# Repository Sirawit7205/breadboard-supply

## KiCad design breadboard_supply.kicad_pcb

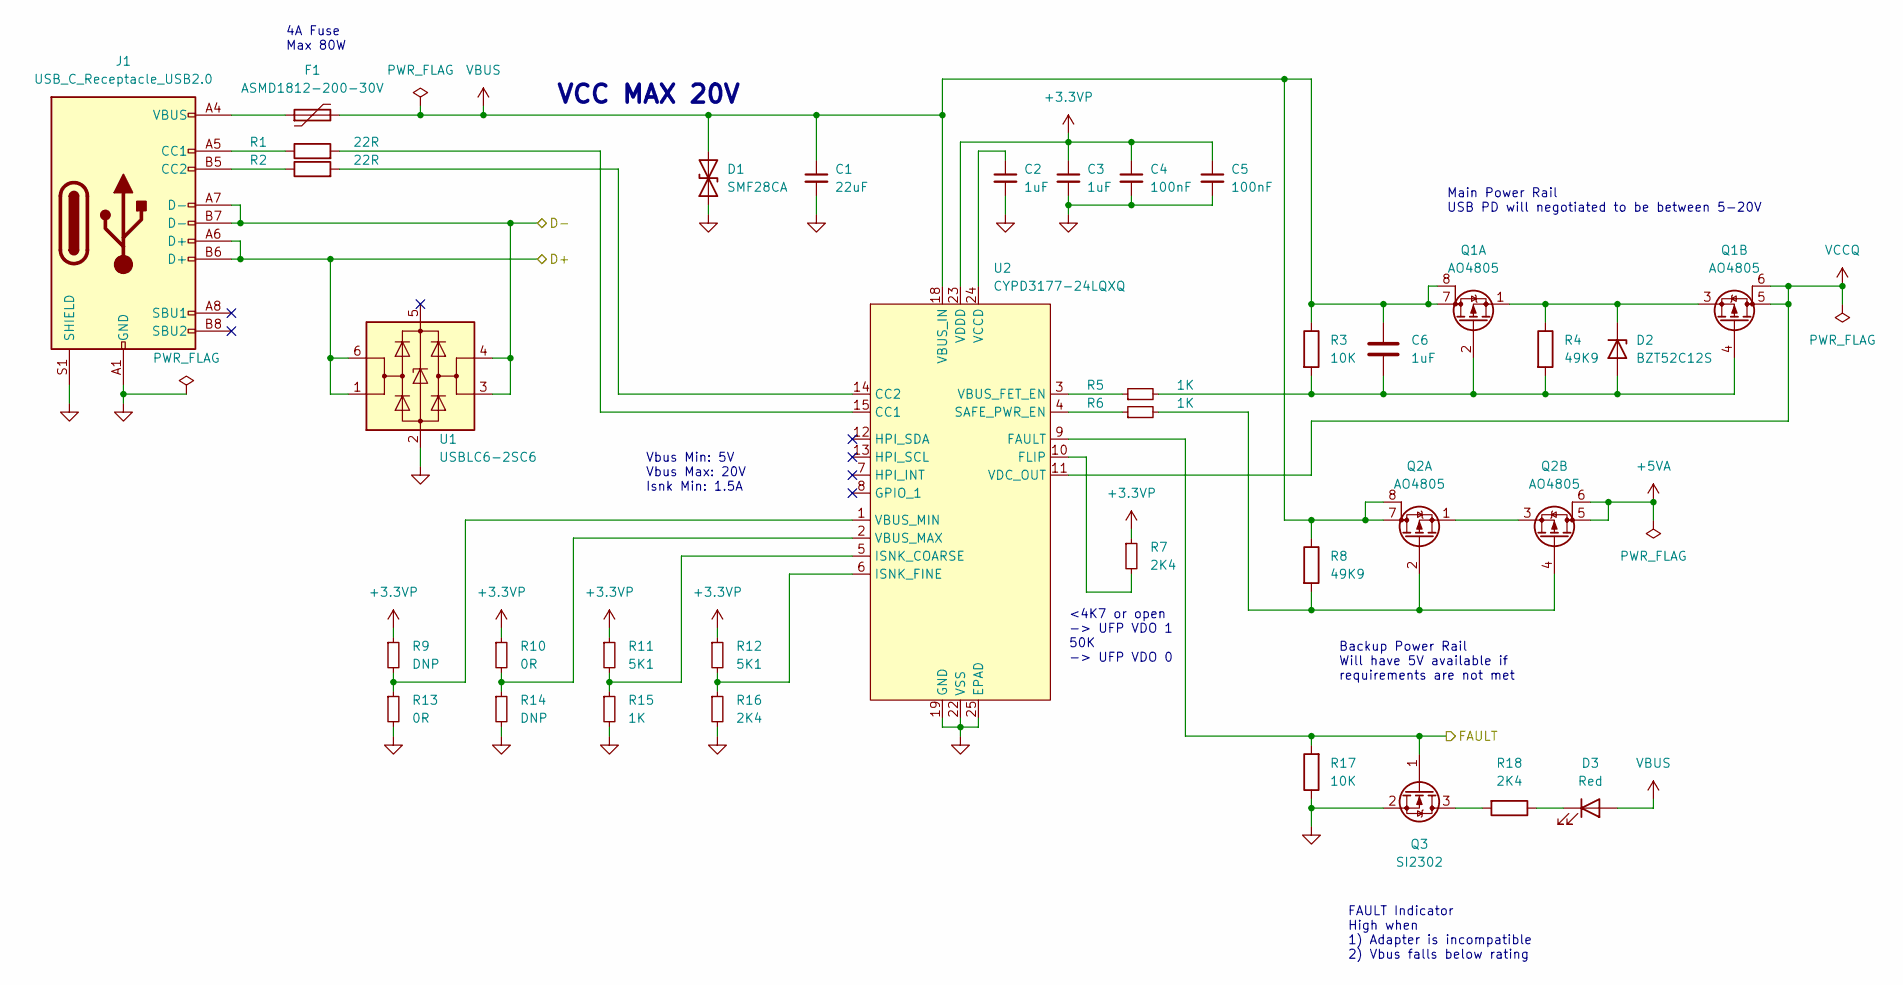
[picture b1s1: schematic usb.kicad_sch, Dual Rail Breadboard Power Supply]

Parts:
C1: 22uF; C_1210_3225Metric; MPN 22uF 25V X7R
C2, C3, C6: 1uF; C_0603_1608Metric; MPN 1uF 50V X7R
C4, C5: 100nF; C_0603_1608Metric; MPN 100nF 50V X7R
D1: SMF28CA; D_SOD-123; MPN SMF28CA
D2: BZT52C12S; D_SOD-323; MPN BZT52C12S
D3: Red; LED_0603_1608Metric; MPN KT-0603R
F1: ASMD1812-200-30V; Fuse_1812_4532Metric; MPN ASMD1812-200-30V
J1: USB_C_Receptacle_USB2.0; USB_C_Receptacle_HRO_TYPE-C-31-M-12_NO_SBU_CircularHoles; MPN HC-TYPE-C-16P-01A
Q1, Q2: AO4805; SOIC-8_3.9x4.9mm_P1.27mm; MPN AO4805
Q3: SI2302; SOT-23
R1, R2: 22R; R_0603_1608Metric; MPN 22R 1%
R3, R17: 10K; R_0603_1608Metric; MPN 10K 1%
R4, R8: 49K9; R_0603_1608Metric; MPN 49K9 1%
R5, R6, R15: 1K; R_0603_1608Metric; MPN 1K 1%
R7: 2K4; R_0603_1608Metric; MPN 3K3 1%
R9, R14: DNP; R_0603_1608Metric
R10, R13: 0R; R_0603_1608Metric; MPN 0R 1%
R11, R12: 5K1; R_0603_1608Metric; MPN 5K1 1%
R16, R18: 2K4; R_0603_1608Metric; MPN 2K4 1%
U1: USBLC6-2SC6; SOT-23-6; MPN USBLC6-2SC6
U2: CYPD3177-24LQXQ; QFN-24-1EP_4x4mm_P0.5mm_EP2.7x2.7mm; MPN CYPD3177-24LQXQ

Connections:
+3.3VP: C3.1, C4.1, C5.1, R7.1, R9.1, R10.1, R11.1, R12.1, U2.23 (VDDD)
+5VA: Q2.5 (D), Q2.6 (G); also elsewhere on the board
/Microcontroller/D+: J1.A6 (D+), J1.B6 (D+), U1.1 (I/O1), U1.6 (I/O1); also elsewhere on the board
/Microcontroller/D-: J1.A7 (D-), J1.B7 (D-), U1.3 (I/O2), U1.4 (I/O2); also elsewhere on the board
/Microcontroller/PD_FAULT: Q3.1 (G), R17.2, U2.9 (FAULT); also elsewhere on the board
GND: C1.2, C2.2, C3.2, C4.2, C5.2, D1.1 (A1), J1.A1 (GND), J1.A12 (GND), J1.B1 (GND), J1.B12 (GND), J1.S1 (SHIELD), Q3.2 (S), R13.2, R14.2, R15.2, R16.2, R17.1, U1.2 (GND), U2.19 (GND), U2.22 (VSS), U2.25 (EPAD); also elsewhere on the board
unnamed: C2.1, U2.24 (VCCD)
unnamed: C6.2, D2.2 (A), Q1.2 (G), Q1.4 (G), R3.2, R4.2, R5.2
unnamed: D2.1 (K), Q1.1 (S), Q1.3 (S), R4.1
unnamed: D3.1 (K), R18.1
unnamed: F1.1, J1.A4 (VBUS), J1.A9 (VBUS), J1.B4 (VBUS), J1.B9 (VBUS)
unnamed: J1.A5 (CC1), R1.1
unnamed: J1.B5 (CC2), R2.1
unnamed: Q2.1 (S), Q2.3 (S)
unnamed: Q2.2 (G), Q2.4 (G), R6.2, R8.2
unnamed: Q3.3 (D), R18.2
unnamed: R1.2, U2.15 (CC1)
unnamed: R2.2, U2.14 (CC2)
unnamed: R5.1, U2.3 (VBUS_FET_EN)
unnamed: R6.1, U2.4 (SAFE_PWR_EN)
unnamed: R7.2, U2.10 (FLIP)
unnamed: R10.2, R14.1, U2.2 (VBUS_MAX)
unnamed: R11.2, R15.1, U2.5 (ISNK_COARSE)
unnamed: R12.2, R16.1, U2.6 (ISNK_FINE)
unnamed: R9.2, R13.1, U2.1 (VBUS_MIN)
VBUS: C1.1, C6.1, D1.2 (A2), D3.2 (A), F1.2, Q1.7 (D), Q1.8 (G), Q2.7 (D), Q2.8 (G), R3.1, R8.1, U2.18 (VBUS_IN)
VCCQ: Q1.5 (D), Q1.6 (G), U2.11 (VDC_OUT); also elsewhere on the board

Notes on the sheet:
Vbus Min: 5V Vbus Max: 20V Isnk Min: 1.5A
4A Fuse Max 80W
Main Power Rail USB PD will negotiated to be between 5-20V
VCC MAX 20V
<4K7 or open -> UFP VDO 1 50K -> UFP VDO 0
FAULT Indicator High when 1) Adapter is incompatible 2) Vbus falls below rating
Backup Power Rail Will have 5V available if requirements are not met

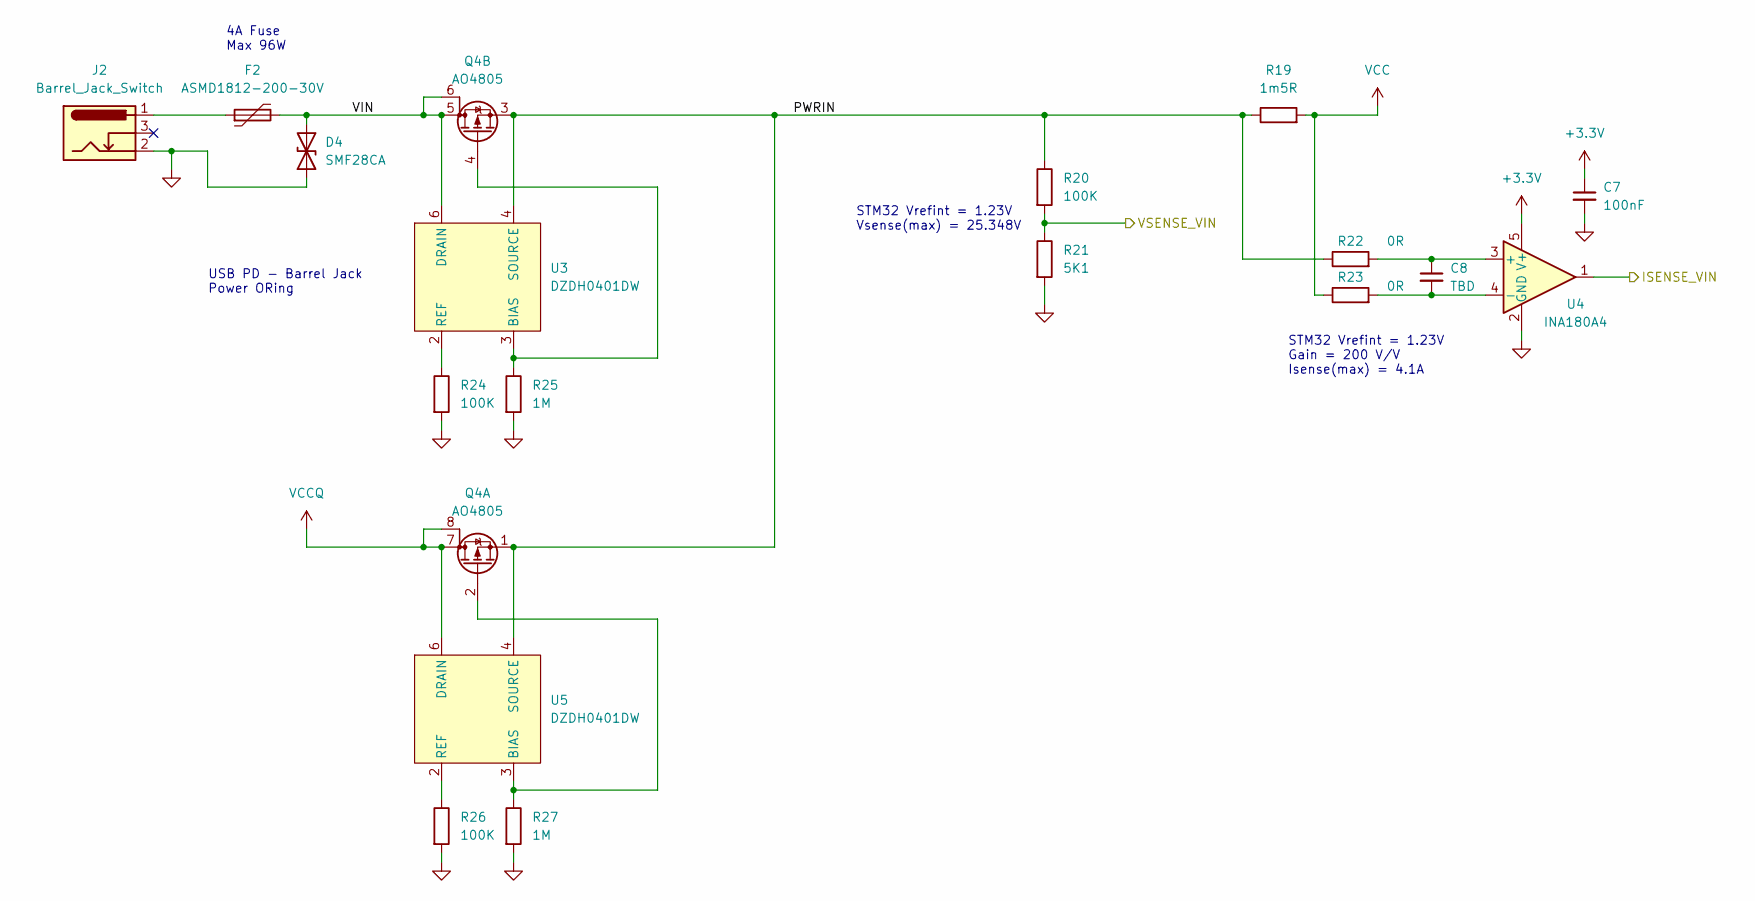
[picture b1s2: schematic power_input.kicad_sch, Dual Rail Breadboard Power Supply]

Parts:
C7: 100nF; C_0603_1608Metric; MPN 100nF 50V X7R
C8: TBD; C_0603_1608Metric
D4: SMF28CA; D_SOD-123; MPN SMF28CA
F2: ASMD1812-200-30V; Fuse_1812_4532Metric; MPN ASMD1812-200-30V
J2: Barrel_Jack_Switch; BarrelJack_Horizontal; MPN DC-005-5A-2.0
Q4: AO4805; SOIC-8_3.9x4.9mm_P1.27mm; MPN AO4805
R19: 1m5R; R_2512_6332Metric; MPN 1m5R 1%
R20, R24, R26: 100K; R_0603_1608Metric; MPN 100K 1%
R21: 5K1; R_0603_1608Metric; MPN 5K1 1%
R22, R23: 0R; R_0603_1608Metric; MPN 0R 1%
R25, R27: 1M; R_0603_1608Metric; MPN 1M 1%
U3, U5: DZDH0401DW; SOT-363_SC-70-6; MPN DZDH0401DW-7
U4: INA180A4; SOT-23-5; MPN INA180A4IDBVR

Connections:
+3.3V: C7.1, U4.5 (V+); also elsewhere on the board
/Microcontroller/ISENSE_VIN: U4.1; also elsewhere on the board
/Microcontroller/VSENSE_VIN: R20.2, R21.1; also elsewhere on the board
/Power Input/PWRIN: Q4.1 (S), Q4.3 (S), R19.1, R20.1, R22.1, U3.4 (SOURCE), U5.4 (SOURCE)
/Power Input/VIN: D4.2 (A2), F2.2, Q4.5 (D), Q4.6 (G), U3.6 (DRAIN)
GND: C7.2, D4.1 (A1), J2.2, R21.2, R24.2, R25.2, R26.2, R27.2, U4.2 (GND); also elsewhere on the board
unnamed: C8.1, R22.2, U4.3 (+)
unnamed: C8.2, R23.2, U4.4 (-)
unnamed: F2.1, J2.1
unnamed: Q4.2 (G), R27.1, U5.3 (BIAS)
unnamed: Q4.4 (G), R25.1, U3.3 (BIAS)
unnamed: R24.1, U3.2 (REF)
unnamed: R26.1, U5.2 (REF)
VCC: R19.2, R23.1; also elsewhere on the board
VCCQ: Q4.7 (D), Q4.8 (G), U5.6 (DRAIN); also elsewhere on the board

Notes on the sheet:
4A Fuse Max 96W
STM32 Vrefint = 1.23V Vsense(max) = 25.348V
STM32 Vrefint = 1.23V Gain = 200 V/V Isense(max) = 4.1A
USB PD - Barrel Jack Power ORing

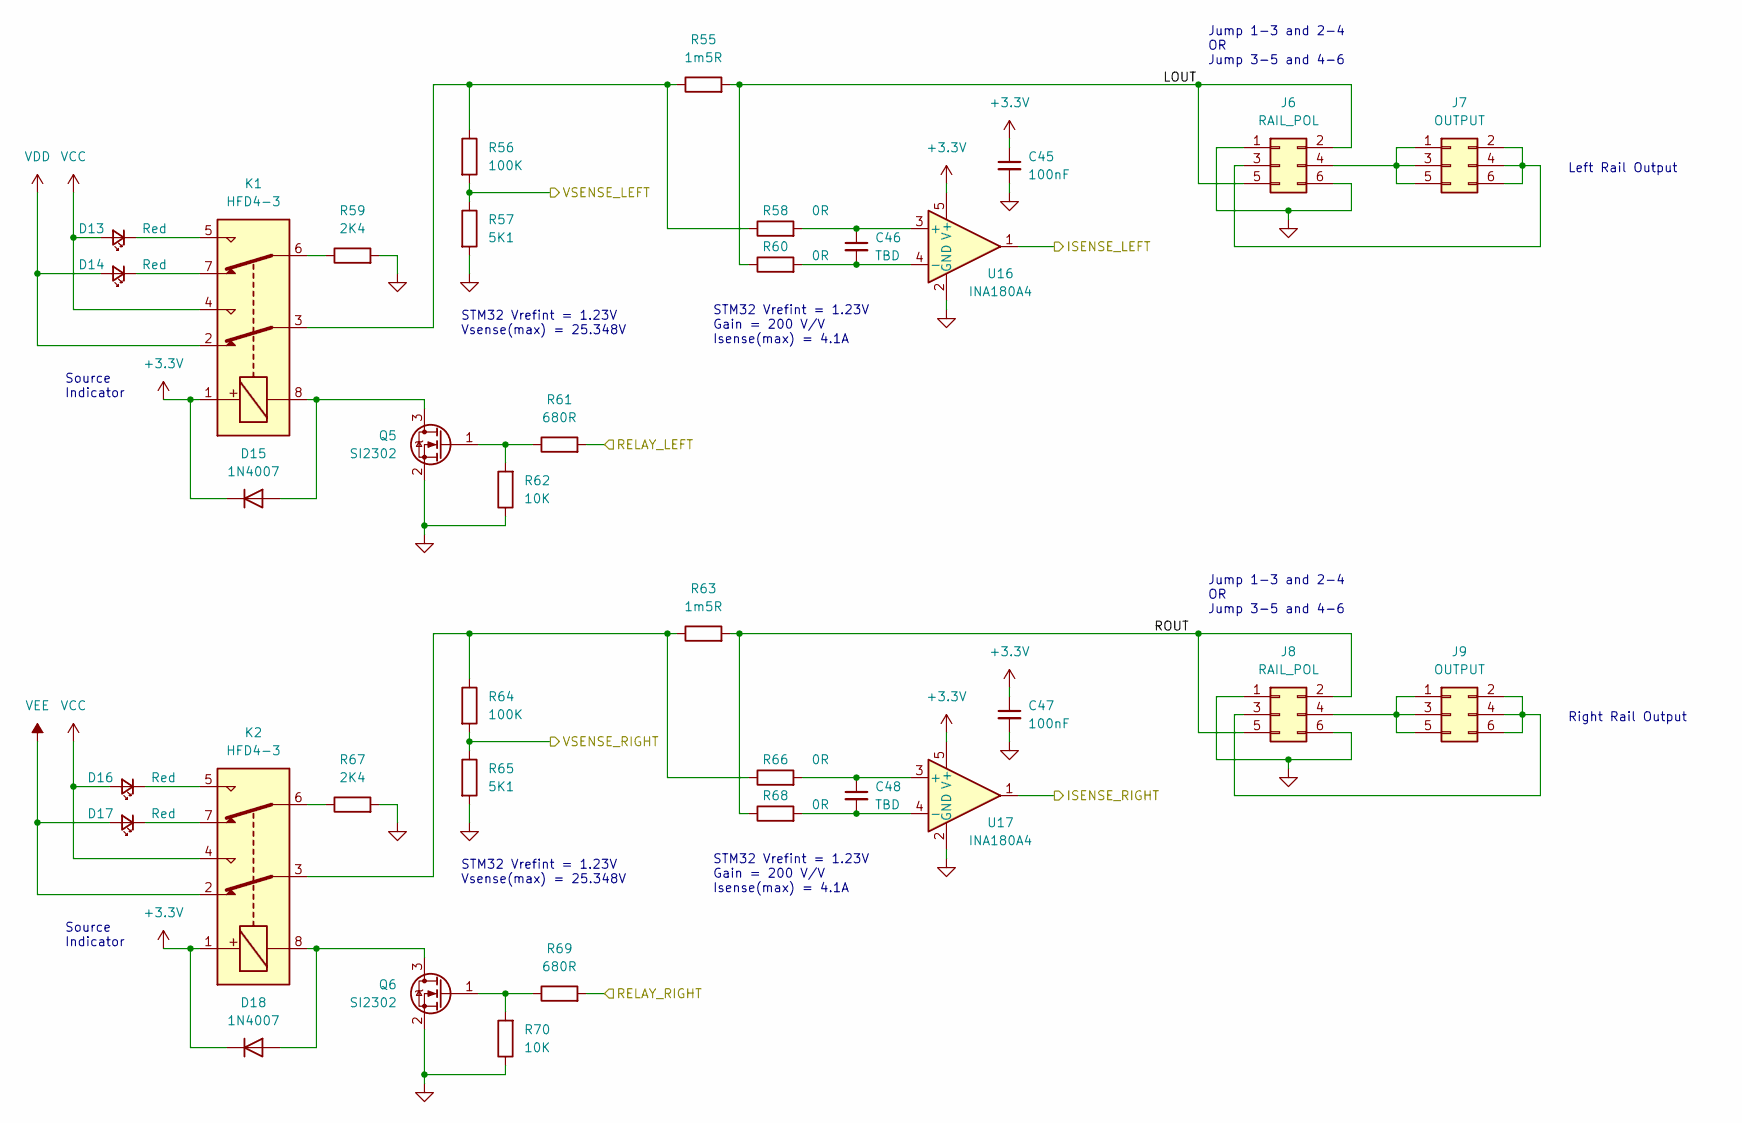
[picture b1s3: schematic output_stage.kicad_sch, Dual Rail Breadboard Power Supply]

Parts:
C45, C47: 100nF; C_0603_1608Metric; MPN 100nF 50V X7R
C46, C48: TBD; C_0603_1608Metric
D13, D14, D16, D17: Red; LED_0603_1608Metric; MPN KT-0603R
D15, D18: 1N4007; D_SOD-123; MPN A7
J6, J8: RAIL_POL; PinHeader_2x03_P2.54mm_Vertical
J7, J9: OUTPUT; PinHeader_2x03_P2.54mm_Vertical
K1, K2: HFD4-3; HFD4; MPN HFD4/3-SR
Q5, Q6: SI2302; SOT-23; MPN SI2302
R55, R63: 1m5R; R_2512_6332Metric; MPN 1m5R 1%
R56, R64: 100K; R_0603_1608Metric; MPN 100K 1%
R57, R65: 5K1; R_0603_1608Metric; MPN 5K1 1%
R58, R60, R66, R68: 0R; R_0603_1608Metric; MPN 0R 1%
R59, R67: 2K4; R_0603_1608Metric; MPN 2K4 1%
R61, R69: 680R; R_0603_1608Metric; MPN 680R 1%
R62, R70: 10K; R_0603_1608Metric; MPN 10K 1%
U16, U17: INA180A4; SOT-23-5; MPN INA180A4IDBVR

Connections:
+3.3V: C45.1, C47.1, D15.1 (K), D18.1 (K), K1.1, K2.1, U16.5 (V+), U17.5 (V+); also elsewhere on the board
/Microcontroller/ISENSE_LEFT: U16.1; also elsewhere on the board
/Microcontroller/ISENSE_RIGHT: U17.1; also elsewhere on the board
/Microcontroller/RELAY_LEFT: R61.2; also elsewhere on the board
/Microcontroller/RELAY_RIGHT: R69.2; also elsewhere on the board
/Microcontroller/VSENSE_LEFT: R56.2, R57.1; also elsewhere on the board
/Microcontroller/VSENSE_RIGHT: R64.2, R65.1; also elsewhere on the board
/Output Stage/LOUT: J6.2, J6.5, R55.2, R60.1
/Output Stage/ROUT: J8.2, J8.5, R63.2, R68.1
GND: C45.2, C47.2, J6.1, J6.6, J8.1, J8.6, Q5.2 (S), Q6.2 (S), R57.2, R59.2, R62.1, R65.2, R67.2, R70.1, U16.2 (GND), U17.2 (GND); also elsewhere on the board
unnamed: C46.1, R58.2, U16.3 (+)
unnamed: C46.2, R60.2, U16.4 (-)
unnamed: C48.1, R66.2, U17.3 (+)
unnamed: C48.2, R68.2, U17.4 (-)
unnamed: D13.1 (K), K1.5
unnamed: D14.1 (K), K1.7
unnamed: D15.2 (A), K1.8, Q5.3 (D)
unnamed: D16.1 (K), K2.5
unnamed: D17.1 (K), K2.7
unnamed: D18.2 (A), K2.8, Q6.3 (D)
unnamed: J6.3, J7.2, J7.4, J7.6
unnamed: J6.4, J7.1, J7.3, J7.5
unnamed: J8.3, J9.2, J9.4, J9.6
unnamed: J8.4, J9.1, J9.3, J9.5
unnamed: K1.3, R55.1, R56.1, R58.1
unnamed: K1.6, R59.1
unnamed: K2.3, R63.1, R64.1, R66.1
unnamed: K2.6, R67.1
unnamed: Q5.1 (G), R61.1, R62.2
unnamed: Q6.1 (G), R69.1, R70.2
VCC: D13.2 (A), D16.2 (A), K1.4, K2.4; also elsewhere on the board
VDD: D14.2 (A), K1.2; also elsewhere on the board
VEE: D17.2 (A), K2.2; also elsewhere on the board

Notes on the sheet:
STM32 Vrefint = 1.23V Vsense(max) = 25.348V
Left Rail Output
Source Indicator
Right Rail Output
Jump 1-3 and 2-4 OR Jump 3-5 and 4-6
STM32 Vrefint = 1.23V Gain = 200 V/V Isense(max) = 4.1A

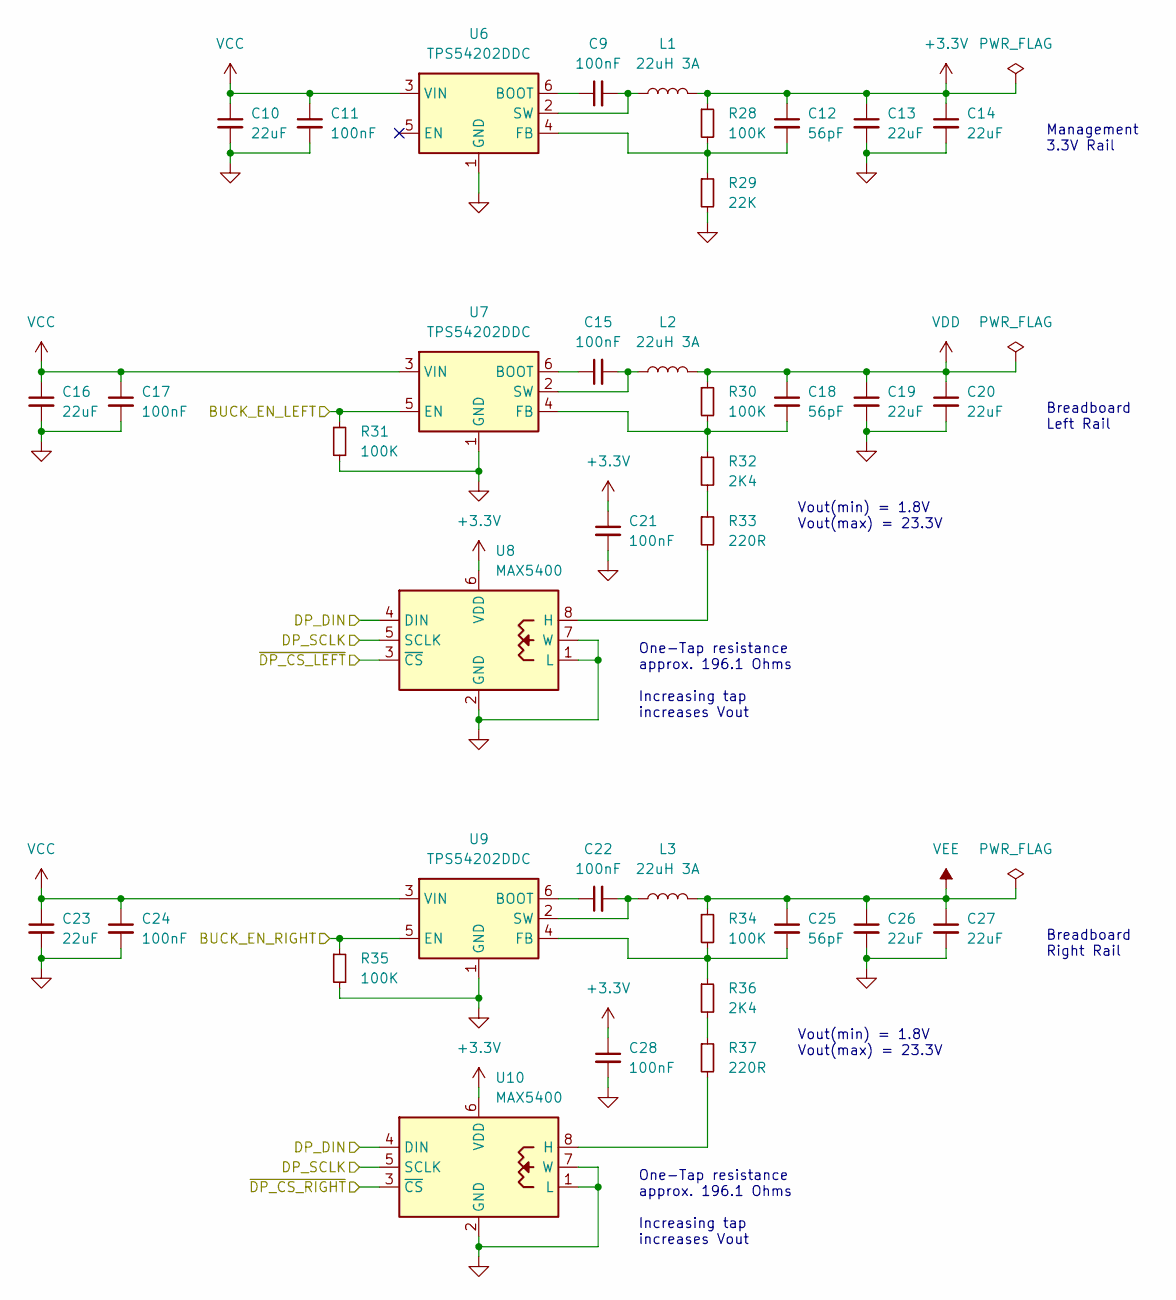
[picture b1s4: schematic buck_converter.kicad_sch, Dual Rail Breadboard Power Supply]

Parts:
C9, C11, C15, C17, C21, C22, C24, C28: 100nF; C_0603_1608Metric; MPN 100nF 50V X7R
C10, C13, C14, C16, C19, C20, C23, C26, C27: 22uF; C_1210_3225Metric; MPN 22uF 25V X7R
C12, C18, C25: 56pF; C_0603_1608Metric; MPN 56pF 50V C0G
L1, L2, L3: 22uH 3A; L_Bourns_SRN6045TA; MPN SRN6045TA-220M
R28, R30, R31, R34, R35: 100K; R_0603_1608Metric; MPN 100K 1%
R29: 22K; R_0603_1608Metric; MPN 22K 1%
R32, R36: 2K4; R_0603_1608Metric; MPN 2K4 1%
R33, R37: 220R; R_0603_1608Metric; MPN 220R 1%
U6, U7, U9: TPS54202DDC; SOT-23-6; MPN TPS54202DDCR
U8, U10: MAX5400; SOT-23-8; MPN MAX5400EKA+T

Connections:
+3.3V: C12.1, C13.1, C14.1, C21.1, C28.1, L1.2, R28.1, U8.6 (VDD), U10.6 (VDD); also elsewhere on the board
/Buck Converter/BUCK_EN_LEFT: R31.1, U7.5 (EN); also elsewhere on the board
/Buck Converter/BUCK_EN_RIGHT: R35.1, U9.5 (EN); also elsewhere on the board
/Buck Converter/DP_DIN: U8.4 (DIN), U10.4 (DIN); also elsewhere on the board
/Buck Converter/DP_SCLK: U8.5 (SCLK), U10.5 (SCLK); also elsewhere on the board
/Buck Converter/~DP_CS_LEFT: U8.3 (~CS); also elsewhere on the board
/Buck Converter/~DP_CS_RIGHT: U10.3 (~CS); also elsewhere on the board
GND: C10.2, C11.2, C13.2, C14.2, C16.2, C17.2, C19.2, C20.2, C21.2, C23.2, C24.2, C26.2, C27.2, C28.2, R29.2, R31.2, R35.2, U6.1 (GND), U7.1 (GND), U8.1 (L), U8.2 (GND), U8.7 (W), U9.1 (GND), U10.1 (L), U10.2 (GND), U10.7 (W); also elsewhere on the board
unnamed: C9.1, U6.6 (BOOT)
unnamed: C9.2, L1.1, U6.2 (SW)
unnamed: C12.2, R28.2, R29.1, U6.4 (FB)
unnamed: C15.1, U7.6 (BOOT)
unnamed: C15.2, L2.1, U7.2 (SW)
unnamed: C18.2, R30.2, R32.1, U7.4 (FB)
unnamed: C22.1, U9.6 (BOOT)
unnamed: C22.2, L3.1, U9.2 (SW)
unnamed: C25.2, R34.2, R36.1, U9.4 (FB)
unnamed: R32.2, R33.1
unnamed: R33.2, U8.8 (H)
unnamed: R36.2, R37.1
unnamed: R37.2, U10.8 (H)
VCC: C10.1, C11.1, C16.1, C17.1, C23.1, C24.1, U6.3 (VIN), U7.3 (VIN), U9.3 (VIN); also elsewhere on the board
VDD: C18.1, C19.1, C20.1, L2.2, R30.1; also elsewhere on the board
VEE: C25.1, C26.1, C27.1, L3.2, R34.1; also elsewhere on the board

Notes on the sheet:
Vout(min) = 1.8V Vout(max) = 23.3V
Breadboard Right Rail
One-Tap resistance approx. 196.1 Ohms Increasing tap increases Vout
Breadboard Left Rail
Management 3.3V Rail

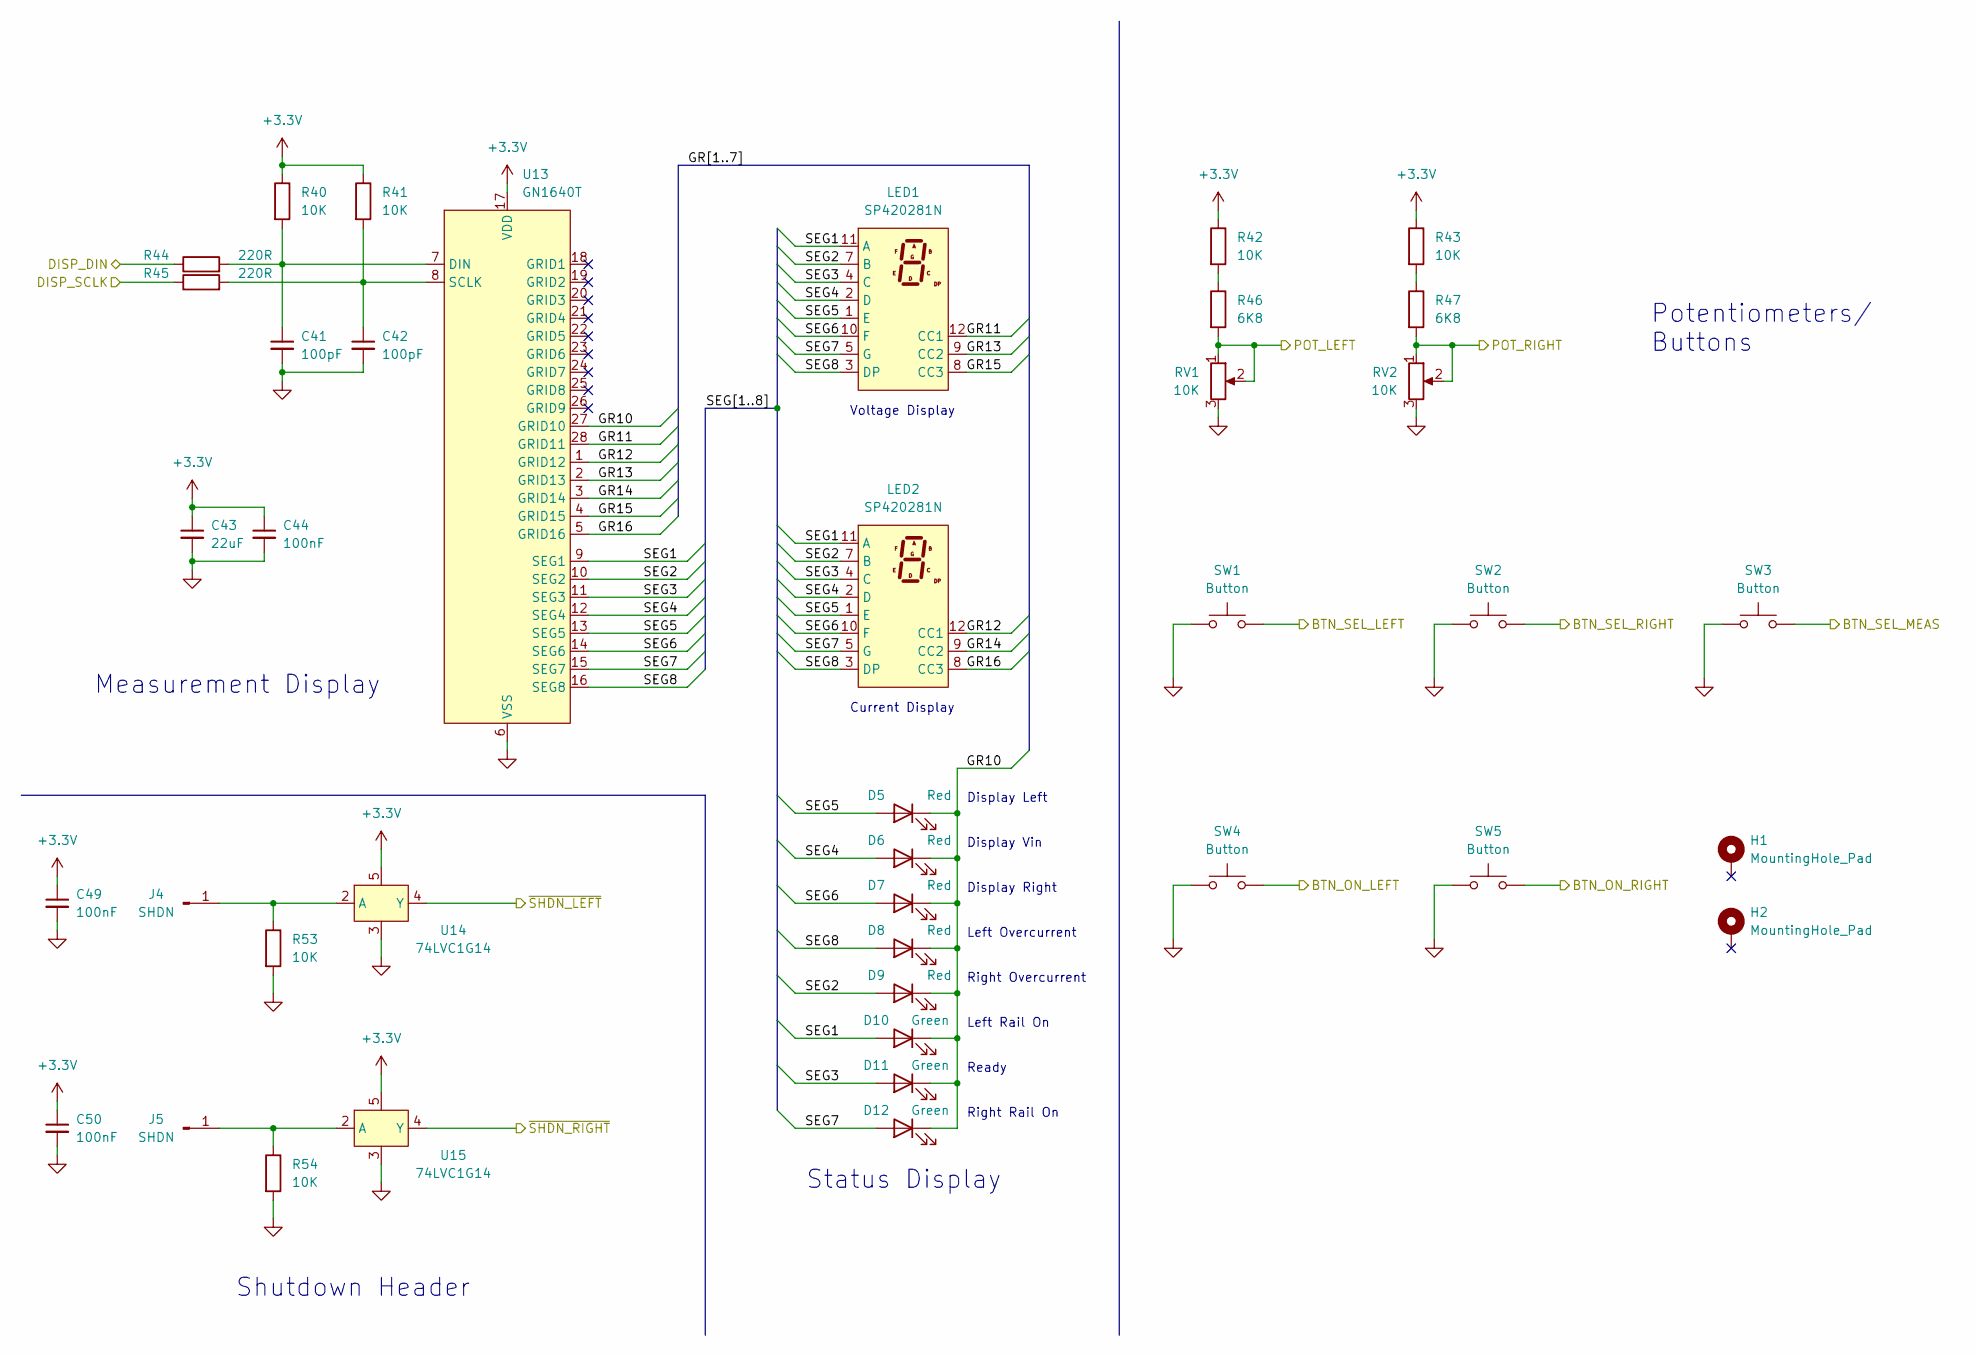
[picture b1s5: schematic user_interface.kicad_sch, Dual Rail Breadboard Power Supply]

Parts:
C41, C42: 100pF; C_0603_1608Metric; MPN 100pF 50V C0G
C43: 22uF; C_1210_3225Metric; MPN 22uF 25V X7R
C44, C49, C50: 100nF; C_0603_1608Metric; MPN 100nF 50V X7R
D5, D6, D7, D8, D9: Red; LED_0603_1608Metric; MPN KT-0603R
D10, D11, D12: Green; LED_0603_1608Metric; MPN 19-217/GHC-YR1S2/3T
H1, H2: MountingHole_Pad; MountingHole_3.2mm_M3_Pad
J4, J5: SHDN; PinHeader_1x01_P2.54mm_Vertical
LED1, LED2: SP420281N; MPN SP420281N
R40, R41, R42, R43, R53, R54: 10K; R_0603_1608Metric; MPN 10K 1%
R44, R45: 220R; R_0603_1608Metric; MPN 220R 1%
R46, R47: 6K8; R_0603_1608Metric; MPN 6K8 1%
RV1, RV2: 10K; Potentiometer_Bourns_3386P_Vertical; MPN 3386P-1-103TLF
SW1, SW2, SW3, SW4, SW5: Button; SW_SPST_CK_RS282G05A3; MPN TS-1101-C-W
U13: GN1640T; SSOP-28_3.9x9.9mm_P0.635mm; MPN GN1640T
U14, U15: 74LVC1G14; SOT-353_SC-70-5; MPN 74LVC1G14GW,125

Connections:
+3.3V: C43.1, C44.1, C49.1, C50.1, R40.1, R41.1, R42.1, R43.1, U13.17 (VDD), U14.5, U15.5; also elsewhere on the board
/Microcontroller/BTN_ON_LEFT: SW4.2; also elsewhere on the board
/Microcontroller/BTN_ON_RIGHT: SW5.2; also elsewhere on the board
/Microcontroller/BTN_SEL_LEFT: SW1.2; also elsewhere on the board
/Microcontroller/BTN_SEL_MEAS: SW3.2; also elsewhere on the board
/Microcontroller/BTN_SEL_RIGHT: SW2.2; also elsewhere on the board
/Microcontroller/POT_LEFT: R46.2, RV1.1, RV1.2; also elsewhere on the board
/Microcontroller/POT_RIGHT: R47.2, RV2.1, RV2.2; also elsewhere on the board
/Microcontroller/SPI2_MOSI: R44.1; also elsewhere on the board
/Microcontroller/SPI2_SCK: R45.1; also elsewhere on the board
/Microcontroller/~SHDN_LEFT: U14.4 (Y); also elsewhere on the board
/Microcontroller/~SHDN_RIGHT: U15.4 (Y); also elsewhere on the board
/User Interface/GR10: D5.1 (K), D6.1 (K), D7.1 (K), D8.1 (K), D9.1 (K), D10.1 (K), D11.1 (K), D12.1 (K), U13.27 (GRID10)
/User Interface/GR11: LED1.12 (CC1), U13.28 (GRID11)
/User Interface/GR12: LED2.12 (CC1), U13.1 (GRID12)
/User Interface/GR13: LED1.9 (CC2), U13.2 (GRID13)
/User Interface/GR14: LED2.9 (CC2), U13.3 (GRID14)
/User Interface/GR15: LED1.8 (CC3), U13.4 (GRID15)
/User Interface/GR16: LED2.8 (CC3), U13.5 (GRID16)
/User Interface/SEG1: D10.2 (A), LED1.11 (A), LED2.11 (A), U13.9 (SEG1)
/User Interface/SEG2: D9.2 (A), LED1.7 (B), LED2.7 (B), U13.10 (SEG2)
/User Interface/SEG3: D11.2 (A), LED1.4 (C), LED2.4 (C), U13.11 (SEG3)
/User Interface/SEG4: D6.2 (A), LED1.2 (D), LED2.2 (D), U13.12 (SEG4)
/User Interface/SEG5: D5.2 (A), LED1.1 (E), LED2.1 (E), U13.13 (SEG5)
/User Interface/SEG6: D7.2 (A), LED1.10 (F), LED2.10 (F), U13.14 (SEG6)
/User Interface/SEG7: D12.2 (A), LED1.5 (G), LED2.5 (G), U13.15 (SEG7)
/User Interface/SEG8: D8.2 (A), LED1.3 (DP), LED2.3 (DP), U13.16 (SEG8)
GND: C41.2, C42.2, C43.2, C44.2, C49.2, C50.2, R53.2, R54.2, RV1.3, RV2.3, SW1.1, SW2.1, SW3.1, SW4.1, SW5.1, U13.6 (VSS), U14.3, U15.3; also elsewhere on the board
unnamed: C41.1, R40.2, R44.2, U13.7 (DIN)
unnamed: C42.1, R41.2, R45.2, U13.8 (SCLK)
unnamed: J4.1, R53.1, U14.2 (A)
unnamed: J5.1, R54.1, U15.2 (A)
unnamed: R42.2, R46.1
unnamed: R43.2, R47.1

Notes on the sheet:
Display Left
Voltage Display
Display Right
Shutdown Header
Left Rail On
Ready
Display Vin
Right Rail On
Right Overcurrent
Current Display
Measurement Display
Potentiometers/ Buttons
Left Overcurrent
Status Display

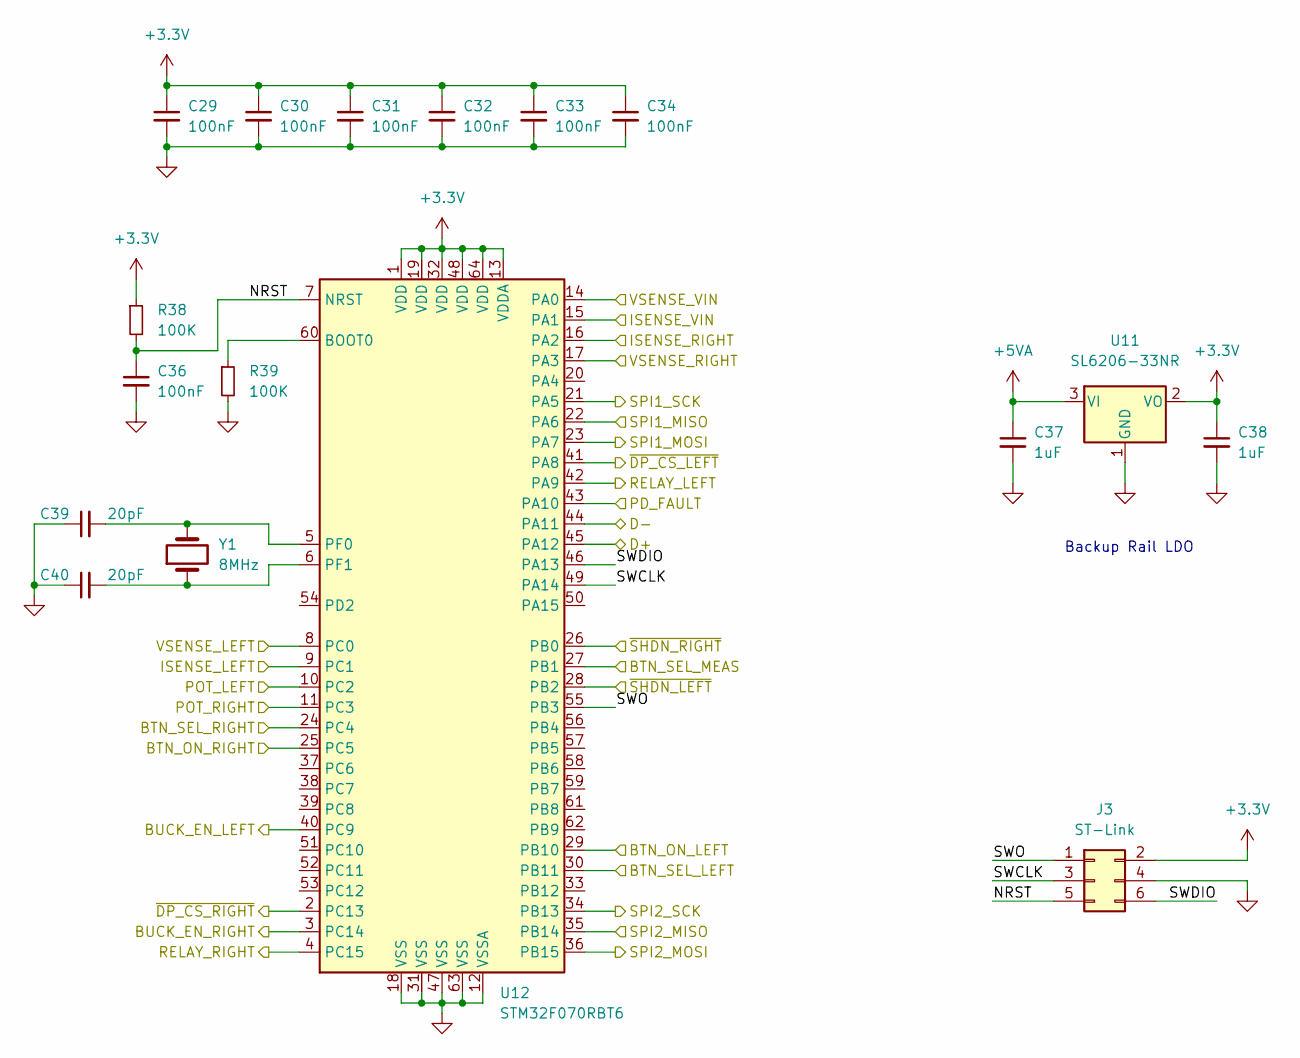
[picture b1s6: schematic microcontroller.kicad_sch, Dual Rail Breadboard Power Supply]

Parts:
C29, C30, C31, C32, C33, C34, C36: 100nF; C_0603_1608Metric; MPN 100nF 50V X7R
C37, C38: 1uF; C_0603_1608Metric; MPN 1uF 50V X7R
C39, C40: 20pF; C_0603_1608Metric; MPN 20pF 50V C0G
J3: ST-Link; PinHeader_2x03_P1.27mm_Vertical_SMD
R38, R39: 100K; R_0603_1608Metric; MPN 100K 1%
U11: SL6206-33NR; SOT-23; MPN XC6206P332MRN
U12: STM32F070RBT6; LQFP-64_10x10mm_P0.5mm; MPN STM32F070RBT6
Y1: 8MHz; Crystal_SMD_5032-2Pin_5.0x3.2mm; MPN ECS-80-8-30-JGN-TR

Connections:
+3.3V: C29.1, C30.1, C31.1, C32.1, C33.1, C34.1, C38.1, J3.2, R38.1, U11.2 (VO), U12.1 (VDD), U12.13 (VDDA), U12.19 (VDD), U12.32 (VDD), U12.48 (VDD), U12.64 (VDD); also elsewhere on the board
+5VA: C37.1, U11.3 (VI); also elsewhere on the board
/Buck Converter/BUCK_EN_LEFT: U12.40 (PC9); also elsewhere on the board
/Buck Converter/BUCK_EN_RIGHT: U12.3 (PC14); also elsewhere on the board
/Buck Converter/DP_DIN: U12.23 (PA7); also elsewhere on the board
/Buck Converter/DP_SCLK: U12.21 (PA5); also elsewhere on the board
/Buck Converter/~DP_CS_LEFT: U12.41 (PA8); also elsewhere on the board
/Buck Converter/~DP_CS_RIGHT: U12.2 (PC13); also elsewhere on the board
/Microcontroller/BTN_ON_LEFT: U12.29 (PB10); also elsewhere on the board
/Microcontroller/BTN_ON_RIGHT: U12.25 (PC5); also elsewhere on the board
/Microcontroller/BTN_SEL_LEFT: U12.30 (PB11); also elsewhere on the board
/Microcontroller/BTN_SEL_MEAS: U12.27 (PB1); also elsewhere on the board
/Microcontroller/BTN_SEL_RIGHT: U12.24 (PC4); also elsewhere on the board
/Microcontroller/D+: U12.45 (PA12); also elsewhere on the board
/Microcontroller/D-: U12.44 (PA11); also elsewhere on the board
/Microcontroller/ISENSE_LEFT: U12.9 (PC1); also elsewhere on the board
/Microcontroller/ISENSE_RIGHT: U12.16 (PA2); also elsewhere on the board
/Microcontroller/ISENSE_VIN: U12.15 (PA1); also elsewhere on the board
/Microcontroller/NRST: C36.1, J3.5, R38.2, U12.7 (NRST)
/Microcontroller/PD_FAULT: U12.43 (PA10); also elsewhere on the board
/Microcontroller/POT_LEFT: U12.10 (PC2); also elsewhere on the board
/Microcontroller/POT_RIGHT: U12.11 (PC3); also elsewhere on the board
/Microcontroller/RELAY_LEFT: U12.42 (PA9); also elsewhere on the board
/Microcontroller/RELAY_RIGHT: U12.4 (PC15); also elsewhere on the board
/Microcontroller/SPI1_MISO: U12.22 (PA6)
/Microcontroller/SPI2_MISO: U12.35 (PB14)
/Microcontroller/SPI2_MOSI: U12.36 (PB15); also elsewhere on the board
/Microcontroller/SPI2_SCK: U12.34 (PB13); also elsewhere on the board
/Microcontroller/SWCLK: J3.3, U12.49 (PA14)
/Microcontroller/SWDIO: J3.6, U12.46 (PA13)
/Microcontroller/SWO: J3.1, U12.55 (PB3)
/Microcontroller/VSENSE_LEFT: U12.8 (PC0); also elsewhere on the board
/Microcontroller/VSENSE_RIGHT: U12.17 (PA3); also elsewhere on the board
/Microcontroller/VSENSE_VIN: U12.14 (PA0); also elsewhere on the board
/Microcontroller/~SHDN_LEFT: U12.28 (PB2); also elsewhere on the board
/Microcontroller/~SHDN_RIGHT: U12.26 (PB0); also elsewhere on the board
GND: C29.2, C30.2, C31.2, C32.2, C33.2, C34.2, C36.2, C37.2, C38.2, C39.1, C40.1, J3.4, R39.2, U11.1 (GND), U12.12 (VSSA), U12.18 (VSS), U12.31 (VSS), U12.47 (VSS), U12.63 (VSS); also elsewhere on the board
unnamed: C39.2, U12.5 (PF0), Y1.2
unnamed: C40.2, U12.6 (PF1), Y1.1
unnamed: R39.1, U12.60 (BOOT0)

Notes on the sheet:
Backup Rail LDO

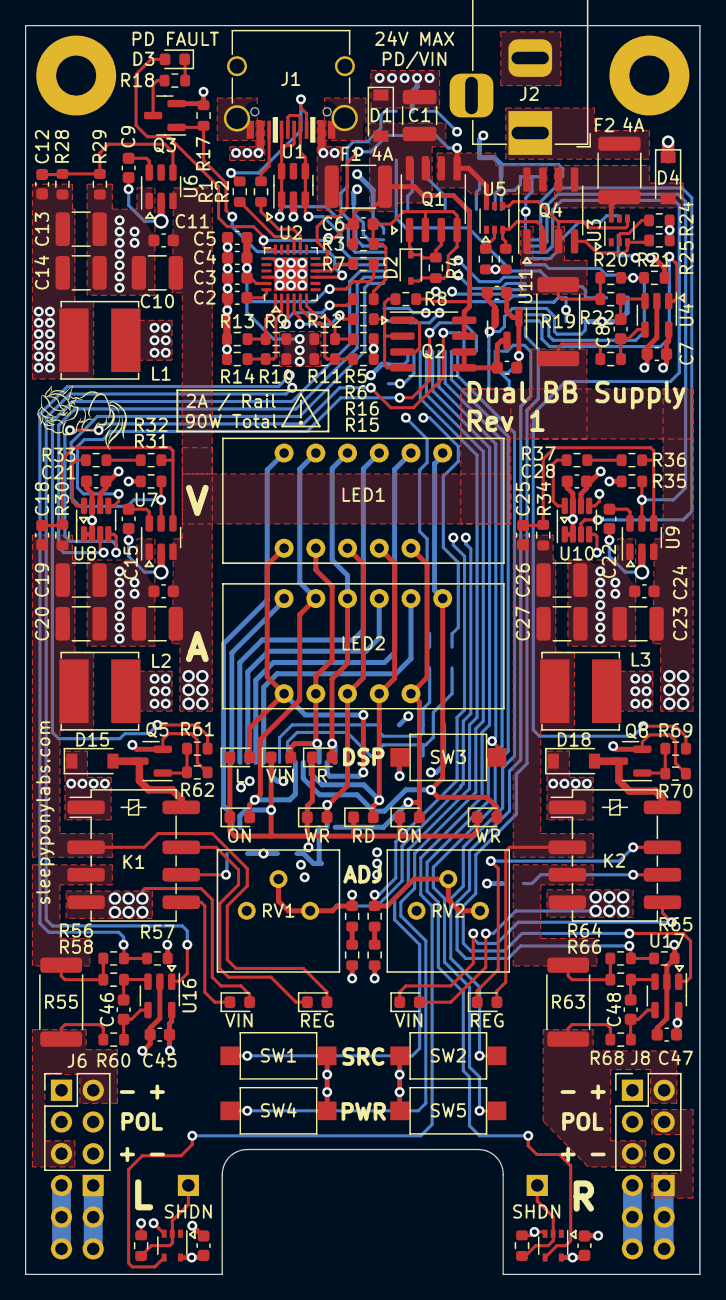
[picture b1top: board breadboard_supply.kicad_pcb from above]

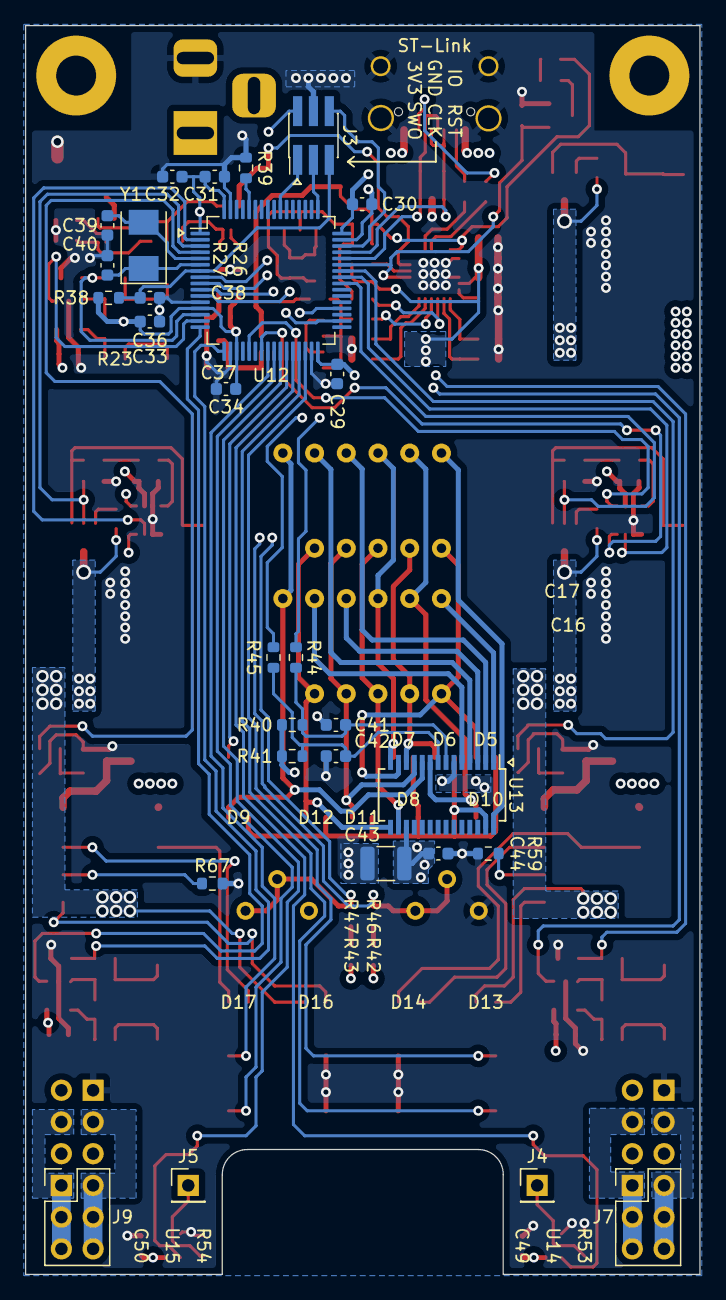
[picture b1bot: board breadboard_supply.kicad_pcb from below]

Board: 4 copper layers, 54.0 x 100.0 mm, 183 parts (29 on the bottom side), 128 nets.

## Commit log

2023-05-28 Initial Commit, PCB WIP
2023-05-30 WIP PCB Routing
2023-05-31 Add mounting holes, WIP routing
2023-06-07 Add information and BOM consolidation for JLCPCB
2023-06-10 Power optimization, add Aisler Assembly MPN info
2023-06-10 Create IBOM, Add sheet info
2023-06-11 Fixed R7 value
